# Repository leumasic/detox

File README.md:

# detox

3x5 column-staggered split keyboard with splayed thumb cluster.

Footprints, symbols and 3d models taken and adapted from multiple sources.

## Credits

inspired by rae dux and dasbob

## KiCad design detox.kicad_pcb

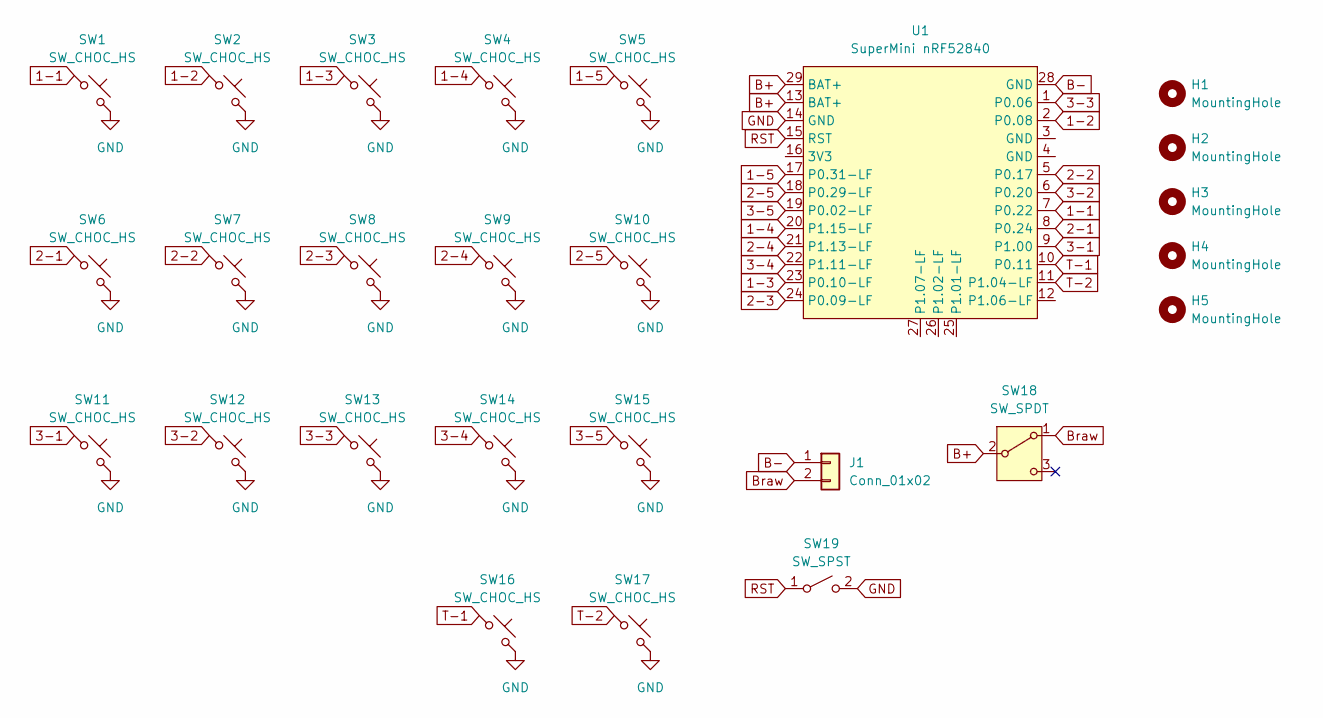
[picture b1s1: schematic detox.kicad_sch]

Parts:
H1, H2, H3, H4, H5: MountingHole; MountingHole_2.2mm_M2
J1: Conn_01x02; JST_PH_S2B-PH-K_1x02_P2.00mm_Horizontal
SW1, SW2, SW3, SW4, SW5, SW6, SW7, SW8, SW9, SW10, SW11, SW12, SW13, SW14, SW15, SW16, SW17: SW_CHOC_HS; SW_choc_v1_v2_HS_1u_reversible
SW18: SW_SPDT; SW_MSK12C02-HB
SW19: SW_SPST
U1: SuperMini nRF52840; SuperMini_nRF52840_AH_Reversible

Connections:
1-1: SW1.1, U1.7 (P0.22)
1-2: SW2.1, U1.2 (P0.08)
1-3: SW3.1, U1.23 (P0.10-LF)
1-4: SW4.1, U1.20 (P1.15-LF)
1-5: SW5.1, U1.17 (P0.31-LF)
2-1: SW6.1, U1.8 (P0.24)
2-2: SW7.1, U1.5 (P0.17)
2-3: SW8.1, U1.24 (P0.09-LF)
2-4: SW9.1, U1.21 (P1.13-LF)
2-5: SW10.1, U1.18 (P0.29-LF)
3-1: SW11.1, U1.9 (P1.00)
3-2: SW12.1, U1.6 (P0.20)
3-3: SW13.1, U1.1 (P0.06)
3-4: SW14.1, U1.22 (P1.11-LF)
3-5: SW15.1, U1.19 (P0.02-LF)
B+: SW18.2 (B), U1.13 (BAT+), U1.29 (BAT+); also elsewhere on the board
B-: J1.1, U1.28 (GND)
Braw: J1.2, SW18.1 (A); also elsewhere on the board
GND: SW1.2, SW2.2, SW3.2, SW4.2, SW5.2, SW6.2, SW7.2, SW8.2, SW9.2, SW10.2, SW11.2, SW12.2, SW13.2, SW14.2, SW15.2, SW16.2, SW17.2, SW19.2 (B), U1.14 (GND)
RST: SW19.1 (A), U1.15 (RST)
T-1: SW16.1, U1.10 (P0.11)
T-2: SW17.1, U1.11 (P1.04-LF)

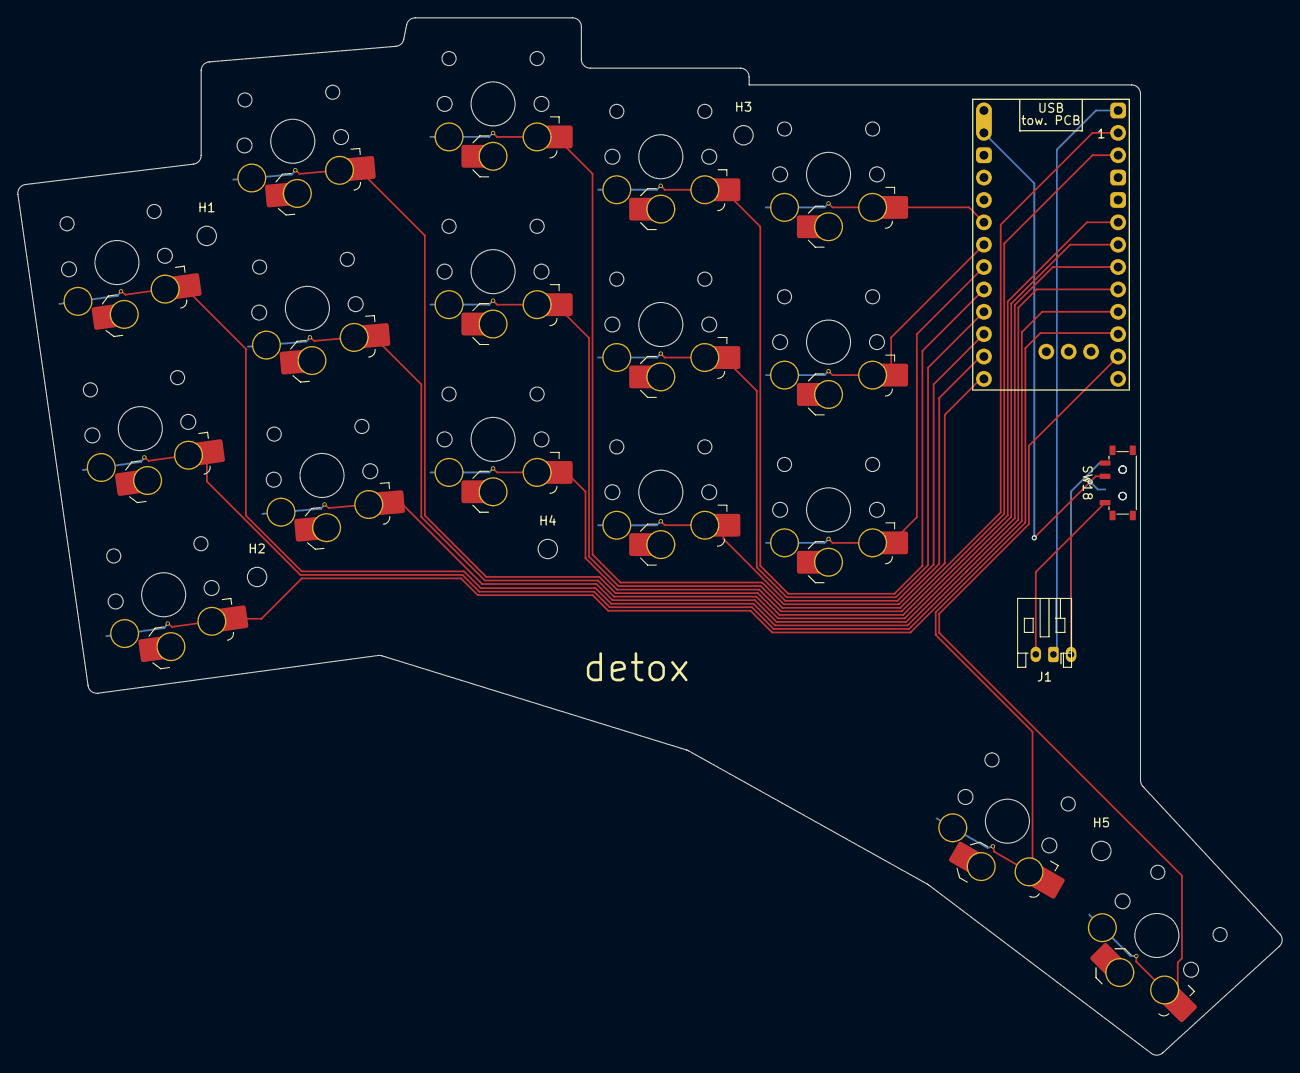
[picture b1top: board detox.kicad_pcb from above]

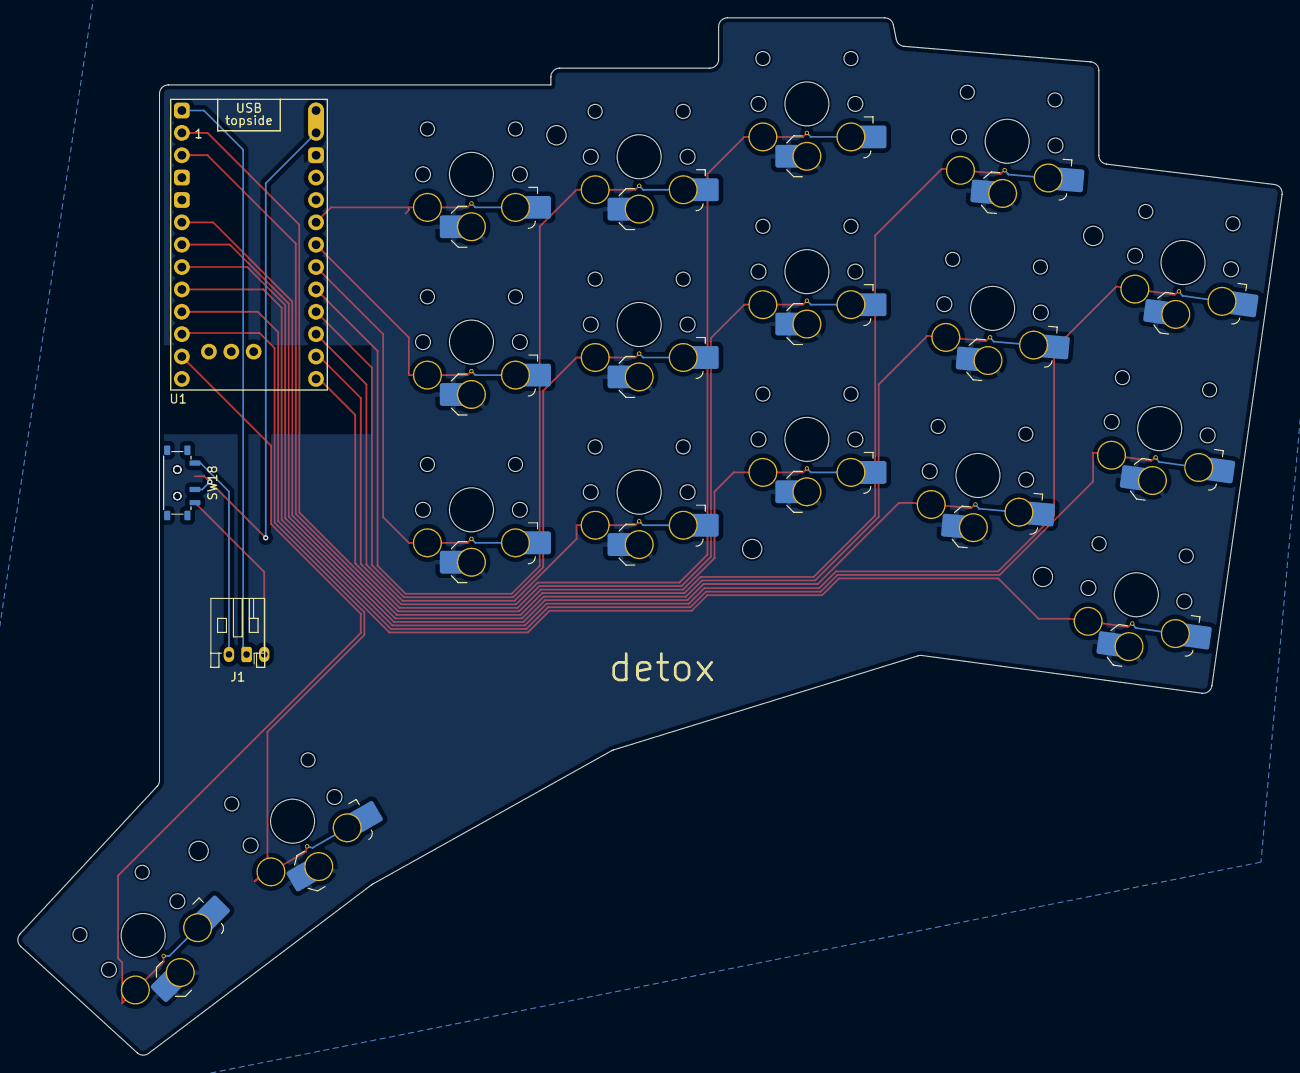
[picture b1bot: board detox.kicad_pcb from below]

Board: 2 copper layers, 143.6 x 117.8 mm, 27 parts (3 on the bottom side), 21 nets.

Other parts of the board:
J1#2: Conn_01x02; JST_PH_S2B-PH-K_1x02_P2.00mm_Horizontal
SW18#2: SW_SPDT; SW_MSK12C02-HB

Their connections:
B+: SW18#2.2 (B); also elsewhere on the board
Braw: J1#2.2, SW18#2.1 (A); also elsewhere on the board

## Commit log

2025-01-11 beautiful, init?
2025-01-12 add README
2025-02-08 add zmk config files
2025-02-08 enable zmk studio over usb
2025-02-08 default ZMK_STUDIO to enabled
2025-02-08 add physical layout
2025-02-08 fix physical layout
2025-02-08 reference physical layout
2025-02-08 import
2025-02-08 parenthesize negative values
2025-02-08 test
2025-02-08 add kscan
2025-03-01 fix detox layout
2025-03-03 improve keymap
2025-03-03 add fn layer and num layer
2025-03-03 faster shift
2025-03-06 keymap update
2025-03-07 add symbols
2025-03-07 update symbols
2025-08-14 update sym layer
